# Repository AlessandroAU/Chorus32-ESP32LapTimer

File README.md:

# Changes:

This fork adds an additional PCB option and assosiated software changes to Chorus32, check out the PCB folder [here](pcb/AaronSmith/PCB%20V2) for more hardware details.

# Chorus32-ESP32Laptimer

This is an ESP32 port of the popular Chorus RF laptimer (https://github.com/voroshkov/Chorus-RF-Laptimer). Using an ESP32 provides much more processing power than AVR based Arduino boards and also has built in Wifi and Bluetooth networking simplifying connectivity options.

Compared to the original ChorusRF Lamptimer this ESP32 version only requires one RX module per pilot and a single ESP32 (nodemcu or similar) board. This allows you to connect your Lap timer wirelessly with no extra hardware required. However, due to ADC constraints, we are limited to 6 pilots per device.

Hardware construction is also simplified as both parts are 3.3v logic and there is no need for level shifting or resistors.

[Click HERE for a video showing the full setup process to get Chorus32 running on your ESP32 using Arduino IDE.](https://www.youtube.com/watch?v=ip2HUVk_lMs).

[Click Here for German version Part 1](https://www.youtube.com/watch?v=z8xTfuLECME) [Part 2](https://www.youtube.com/watch?v=7wl0CgA8YnM).

Updates:
-----
*Important Notice for Chorus32 users!!!:*

As of last commit the default pinout has been changed to match that of the PCBs currently being tested.

For anyone that has built a Chorus32 with original schematics do not worry, your unit will continue working with future updates. However you must change `#define BOARD BOARD_DEFAULT` to `#define BOARD BOARD_OLD` in 'HardwareConfig.h' when compiling.

Added OLED and VBAT measurement support
Auto RSSI threshold setup is also not implemented, just set thresholds manually for now.

Added inital webserver configuration portal
https://www.youtube.com/watch?v=BVd2t0yO_5A/0.jpg

Application Support:
-----
Chorus32 communicates using the Chorus RF Laptimer API, which is supported by LiveTime.

LiveTime is an incredibly powerful and feature-rich timing system which runs on Windows. It is, however, quite complex, and likely overkill for most users.

More information can be found here: https://www.livetimescoring.com/

If you are looking for a simpler setup, you can also use the Chorus RF Lap Timer app available for:

Android: https://play.google.com/store/apps/details?id=app.andrey_voroshkov.chorus_laptimer

iOS: https://itunes.apple.com/us/app/chorus-rf-laptimer/id1296647206?mt=8

Serial to UDP bridge.
-----

To use this wirelessly with livetime you must use a third party application to a bridge vitural serial port with the UDP connection to the timer. The native ethernet TCP mode does not work at the moment. You can use this free application https://www.netburner.com/download/virtual-comm-port-driver-windows-xp-10/?fbclid=IwAR2W9V_YzjuP5_u9U-nJx1x38beFWNR0eRI59QOyYO_-NSePmTnW14kk7yA

Configure it like this:

Hardware:
-----
Construction is easy and only requires some basic point to point wiring of each module to the ESP32 board.

See HardwareConfig.h for pin assignments, it is possible to change any pin assignments apart from ADC channels. Note that pin assignments are GPIO hardware pin numbers and not pin numbers specific to the particular ESP32 development board you may be using.

PCB designs are currently being tested

Performance:
-----
The Chorus32 Lap timer was compared to the $600USD ImmersionRC LapRF 8-Way at a local indoor event, arguably the worst conditions due to multipath and reflections. Results are presented below, you can see that the Chorus32 very closely matches the measured lap times of the LapRF.

## Compiling the project using platformio

## Installing
 TODO

## Compiling and uploading

### IDE
TODO

### CLI
To upload the code to your timer just run
```
pio run -e <your board> -t upload
pio run -e <your board> -t uploadfs
```
Insert the board you are using, which is probably `BOARD_DEFAULT`. To list all valid targets just insert some random string as the board (sorry, I have no idea on how to list them properly).

To update using the webpage, run the same commands (and ignore the errors about a failed connection). The path to the file you upload should now be `<project dir>/.pio/build/<BOARD NAME>/firmware.bin`.

## Compiling the Project using the Arduino IDE (the old way):

#### Add esp32 to the Arduino IDE

Navigate to "File -> Preferences" and add "https://dl.espressif.com/dl/package_esp32_index.json" to "Additional Boards Manager URLs". If there is already an entry, just separate them with a ",".

Now navigate to "Tools -> Board -> Boards Manager..." search for "esp32" and click install.

#### Data Upload

To upload the files for the webpage you'll need to download https://github.com/me-no-dev/arduino-esp32fs-plugin/releases/ and extract it in "<Your Arduino install folder>/tools/". So that you end up with a folder called "ESP32FS" which has a folder "tool" inside of it.

#### Libraries

First head to "Sketch -> Include Library -> Manage Libraries" and search for "adafruit ina219" and "ssd1306 esp32" and install them both. Now head to https://github.com/me-no-dev/ESPAsyncWebServer and https://github.com/me-no-dev/AsyncTCP and click on "Clone or download -> Download ZIP". In the Arduino IDE nagivate to "Sketch -> Include Library -> Add .ZIP Library" and add them both.

#### Flashing
Now hit the upload button (with an arrow to the right) to upload the code to the board. After that upload the webpage data by clicking on "Tools -> ESP32 Sketch Data Upload". This should be done on every update!

You can edit file "HardwareConfig.h" to specify your board type and for some advanced configuration.

#### Updating

For updates either follow the normal flashing procedure or use the web UI.
To use the web UI updater open your Arduino IDE and click the verify button (the most left one).
Depending on your operating system there is a folder named "arduino_build_\<some numbers\>" in:
  - Linux: /tmp
  - Windows: %AppData%
  - OSX: No idea, sorry

Inside that folder should be a file called "ESP32LapTimer.ino.bin", which can be uploaded in the web interface.

Library requirements:
-----
Adafruit_INA219 https://github.com/adafruit/Adafruit_INA219

ESP8266 AND ESP32 OLED DRIVER FOR SSD1306 DISPLAY https://github.com/ThingPulse/esp8266-oled-ssd1306

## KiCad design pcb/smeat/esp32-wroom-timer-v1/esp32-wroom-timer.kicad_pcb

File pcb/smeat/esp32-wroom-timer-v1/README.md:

# Features
 - External edge mounted SMA connector for better range
   - Uses the esp32-wroom-32u
   - To connect the antenna, cut open a U.FL adapter cable and solder one end to the SMA connector
 - Integrated buck converter with correct components ;) (those modules from china are all over the place)
    - Max input 28V (26V if using ina219)
 - Footprint for an optional LoRa module
 - Space for 6 RX5808 modules
 - Optional ina219
    - I don't trust them anymore since one failed for me and put the input voltage on the 3.3V rail
    - Limits input voltage to 26V
 - Optional Fan with optional temperature sensor
 - Beeper

# Bugs
 - Wrong SMA footprint (still fits though)
 - Buzzer footprint is a little bit too small for my buzzers
 - A vertically mounted XT60 might be better

# Images

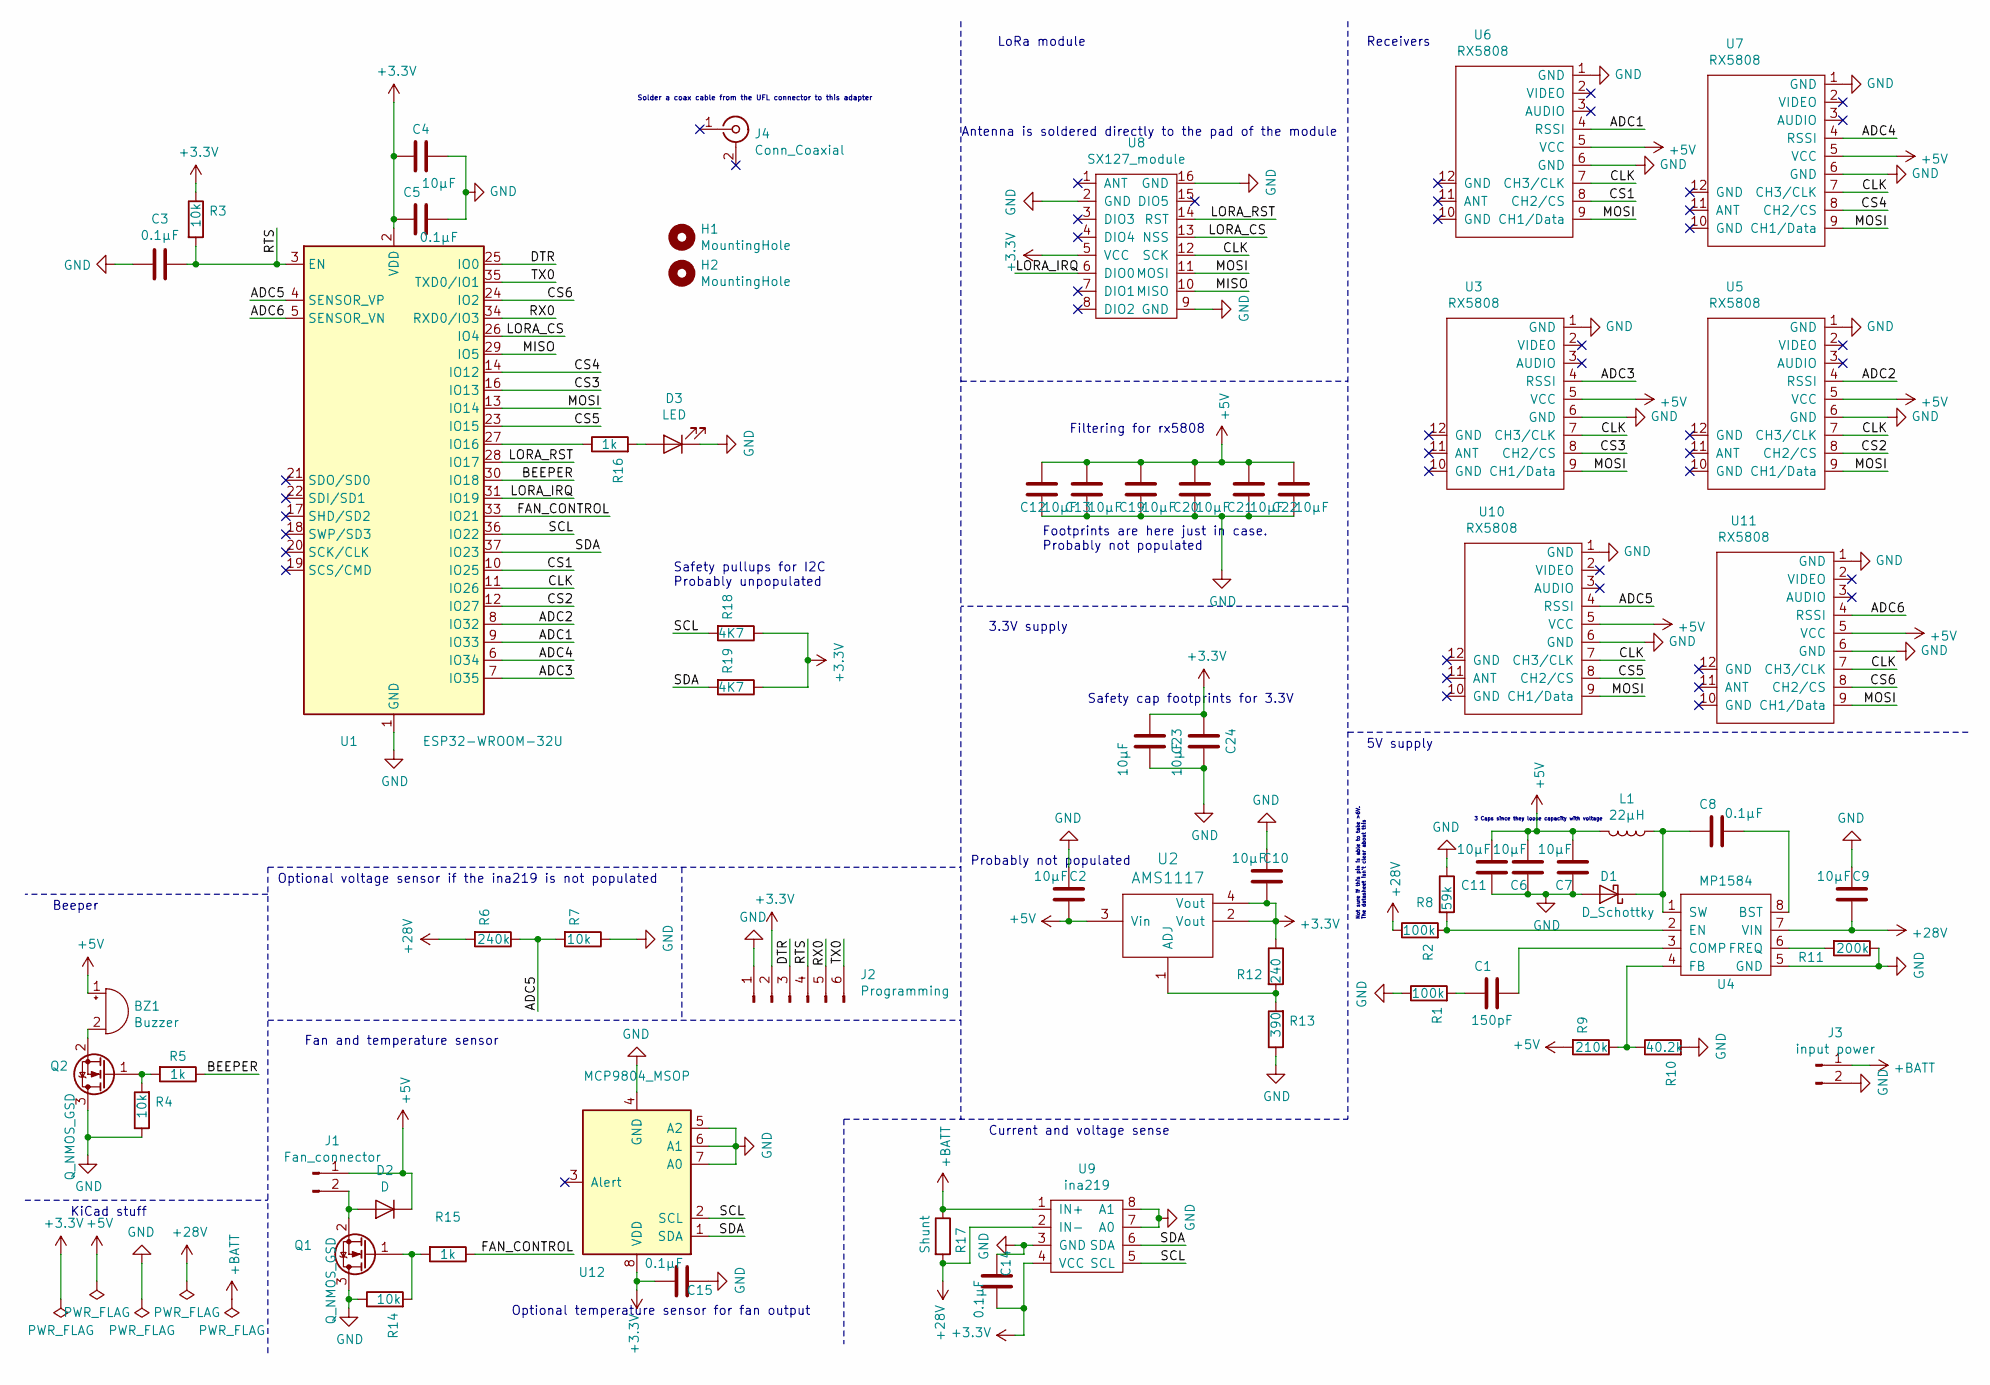
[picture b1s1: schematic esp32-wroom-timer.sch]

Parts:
BZ1: Buzzer; MagneticBuzzer_Kingstate_KCG0601
C1: 150pF; C_0603_1608Metric
C2, C4, C6, C7, C9, C10, C11, C12, C13, C19, C20, C21, C22, C23, C24: 10µF; C_0805_2012Metric
C3, C5, C8, C14, C15: 0.1µF; C_0603_1608Metric
D1: D_Schottky; D_SMA
D2: D; D_SMA
D3: LED; LED_0805_2012Metric
H1, H2: MountingHole; MountingHole_3.2mm_M3
J1: Fan_connector; PinHeader_2x01_P2.00mm_Vertical_SMD
J2: Programming; PinHeader_1x06_P2.00mm_Vertical
J3: input power; SolderWirePad_1x02_P7.62mm_Drill2.5mm
J4: Conn_Coaxial; SMA_Amphenol_132289_EdgeMount
L1: 22µH; L_12x12mm_H6mm
Q1, Q2: Q_NMOS_GSD; SOT-23
R1, R2: 100k; R_0805_2012Metric
R3, R4, R7, R14: 10k; R_0805_2012Metric
R5, R15, R16: 1k; R_0805_2012Metric
R6: 240k; R_0805_2012Metric
R8: 59k; R_0805_2012Metric
R9: 210k; R_0805_2012Metric
R10: 40.2k; R_0805_2012Metric
R11: 200k; R_0805_2012Metric
R12: 240; R_0805_2012Metric
R13: 390; R_0805_2012Metric
R17: Shunt; R_2512_6332Metric
R18, R19: 4K7; R_0805_2012Metric
U1: ESP32-WROOM-32U
U2: AMS1117; SOT-223
U3, U5, U6, U7, U10, U11: RX5808; rx5808
U4: MP1584; SOIC-8_3.9x4.9mm_P1.27mm
U8: SX127_module; sx1276_module
U9: ina219; SOT-23-8
U12: MCP9804_MSOP; MSOP-8_3x3mm_P0.65mm

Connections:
+3V3: C4.2, C5.2, C10.1, C14.1, C15.1, C23.2, C24.2, J2.2, R3.1, R12.1, R18.1, R19.1, U1.2 (VDD), U2.2 (Vout), U2.4 (Vout), U8.5 (VCC), U9.4 (VCC), U12.8 (VDD)
+5V: BZ1.1 (-), C2.1, C6.2, C7.2, C11.2, C12.1, C13.1, C19.1, C20.1, C21.1, C22.1, D2.1 (K), J1.1, L1.2, R9.2, U2.3 (Vin), U3.5 (VCC), U5.5 (VCC), U6.5 (VCC), U7.5 (VCC), U10.5 (VCC), U11.5 (VCC)
+28V: C9.1, R2.1, R6.2, R17.2, U4.7 (VIN), U9.2 (IN-)
+BATT: J3.1, R17.1, U9.1 (IN+)
/ADC1: U1.9 (IO33), U6.4 (RSSI)
/ADC2: U1.8 (IO32), U5.4 (RSSI)
/ADC3: U1.7 (IO35), U3.4 (RSSI)
/ADC4: U1.6 (IO34), U7.4 (RSSI)
/ADC5: R6.1, R7.2, U1.4 (SENSOR_VP), U10.4 (RSSI)
/ADC6: U1.5 (SENSOR_VN), U11.4 (RSSI)
/BEEPER: R5.1, U1.30 (IO18)
/CLK: U1.11 (IO26), U3.7 (CH3/CLK), U5.7 (CH3/CLK), U6.7 (CH3/CLK), U7.7 (CH3/CLK), U8.12 (SCK), U10.7 (CH3/CLK), U11.7 (CH3/CLK)
/CS1: U1.10 (IO25), U6.8 (CH2/CS)
/CS2: U1.12 (IO27), U5.8 (CH2/CS)
/CS3: U1.16 (IO13), U3.8 (CH2/CS)
/CS4: U1.14 (IO12), U7.8 (CH2/CS)
/CS5: U1.23 (IO15), U10.8 (CH2/CS)
/CS6: U1.24 (IO2), U11.8 (CH2/CS)
/DTR: J2.3, U1.25 (IO0)
/FAN_CONTROL: R15.1, U1.33 (IO21)
/LORA_CS: U1.26 (IO4), U8.13 (NSS)
/LORA_IRQ: U1.31 (IO19), U8.6 (DIO0)
/LORA_RST: U1.28 (IO17), U8.14 (RST)
/MISO: U1.29 (IO5), U8.10 (MISO)
/MOSI: U1.13 (IO14), U3.9 (CH1/Data), U5.9 (CH1/Data), U6.9 (CH1/Data), U7.9 (CH1/Data), U8.11 (MOSI), U10.9 (CH1/Data), U11.9 (CH1/Data)
/RTS: C3.1, J2.4, R3.2, U1.3 (EN)
/RX0: J2.5, U1.34 (RXD0/IO3)
/SCL: R18.2, U1.36 (IO22), U9.5 (SCL), U12.2 (SCL)
/SDA: R19.2, U1.37 (IO23), U9.6 (SDA), U12.1 (SDA)
/TX0: J2.6, U1.35 (TXD0/IO1)
GND: C2.2, C3.2, C4.1, C5.1, C6.1, C7.1, C9.2, C10.2, C11.1, C12.2, C13.2, C14.2, C15.2, C19.2, C20.2, C21.2, C22.2, C23.1, C24.1, D1.2 (A), D3.1 (K), J2.1, J3.2, Q1.3 (D), Q2.3 (D), R1.1, R4.1, R7.1, R8.1, R10.2, R11.1, R13.1, R14.1, U1.1 (GND), U1.15 (GND), U1.38 (GND), U3.1 (GND), U3.6 (GND), U4.5 (GND), U5.1 (GND), U5.6 (GND), U6.1 (GND), U6.6 (GND), U7.1 (GND), U7.6 (GND), U8.2 (GND), U8.9 (GND), U8.16 (GND), U9.3 (GND), U9.7 (A0), U9.8 (A1), U10.1 (GND), U10.6 (GND), U11.1 (GND), U11.6 (GND), U12.4 (GND), U12.5 (A2), U12.6 (A1), U12.7 (A0)
unnamed: BZ1.2 (+), Q2.2 (S)
unnamed: C1.1, U4.3 (COMP)
unnamed: C1.2, R1.2
unnamed: C8.1, U4.8 (BST)
unnamed: C8.2, D1.1 (K), L1.1, U4.1 (SW)
unnamed: D2.2 (A), J1.2, Q1.2 (S)
unnamed: D3.2 (A), R16.2
unnamed: Q1.1 (G), R14.2, R15.2
unnamed: Q2.1 (G), R4.2, R5.2
unnamed: R2.2, R8.2, U4.2 (EN)
unnamed: R9.1, R10.1, U4.4 (FB)
unnamed: R11.2, U4.6 (FREQ)
unnamed: R12.2, R13.2, U2.1 (ADJ)
unnamed: R16.1, U1.27 (IO16)

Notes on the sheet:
Antenna is soldered directly to the pad of the module
Filtering for rx5808
Not sure if this pin is able to take >6V. The datasheet isn't clear about this
3 Caps since they loose capacity with voltage
Probably not populated
Footprints are here just in case. Probably not populated
Optional temperature sensor for fan output
KiCad stuff
5V supply
Receivers
Safety cap footprints for 3.3V
3.3V supply
Current and voltage sense
Fan and temperature sensor
Beeper
LoRa module
Optional voltage sensor if the ina219 is not populated
Solder a coax cable from the UFL connector to this adapter
Safety pullups for I2C Probably unpopulated

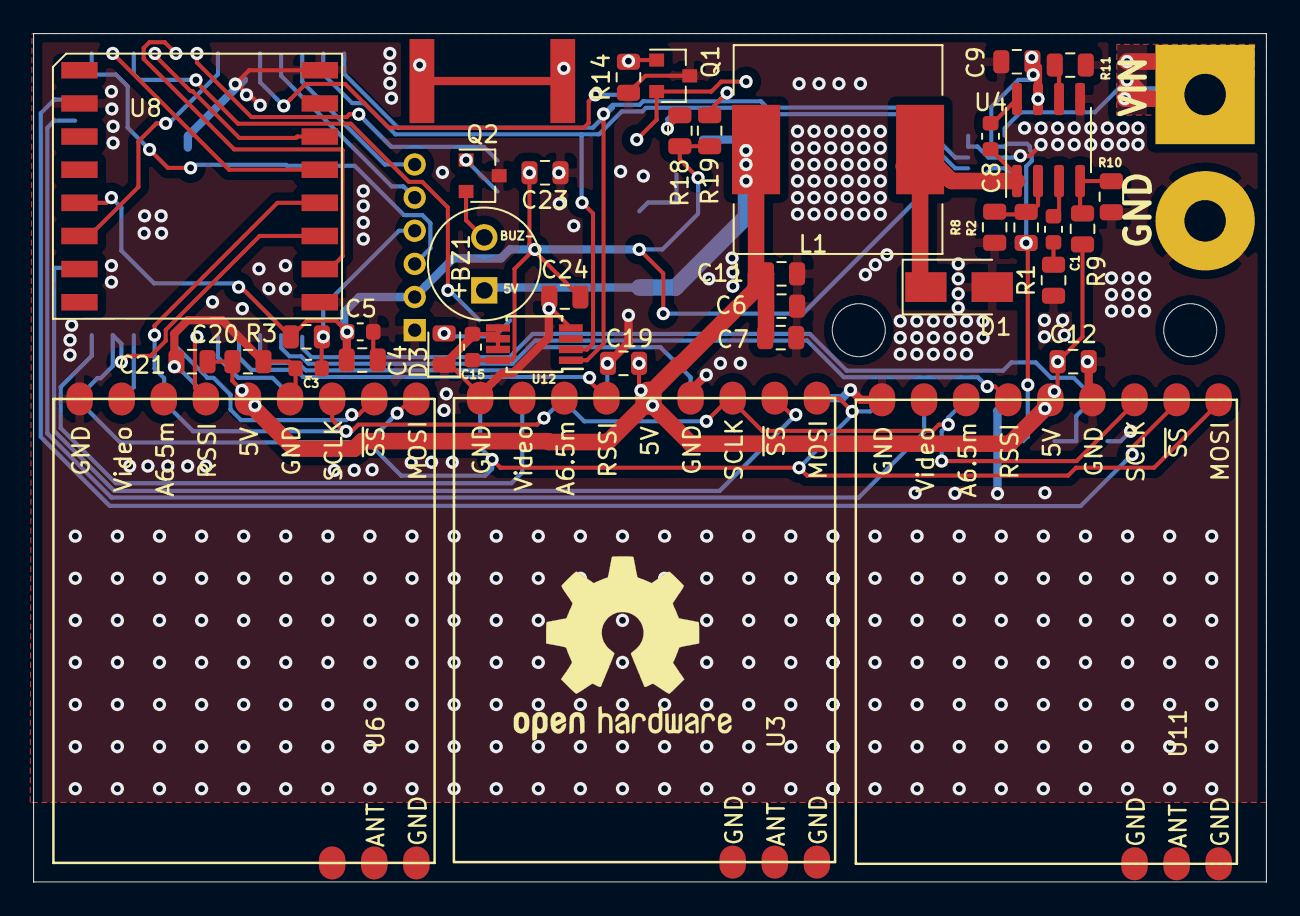
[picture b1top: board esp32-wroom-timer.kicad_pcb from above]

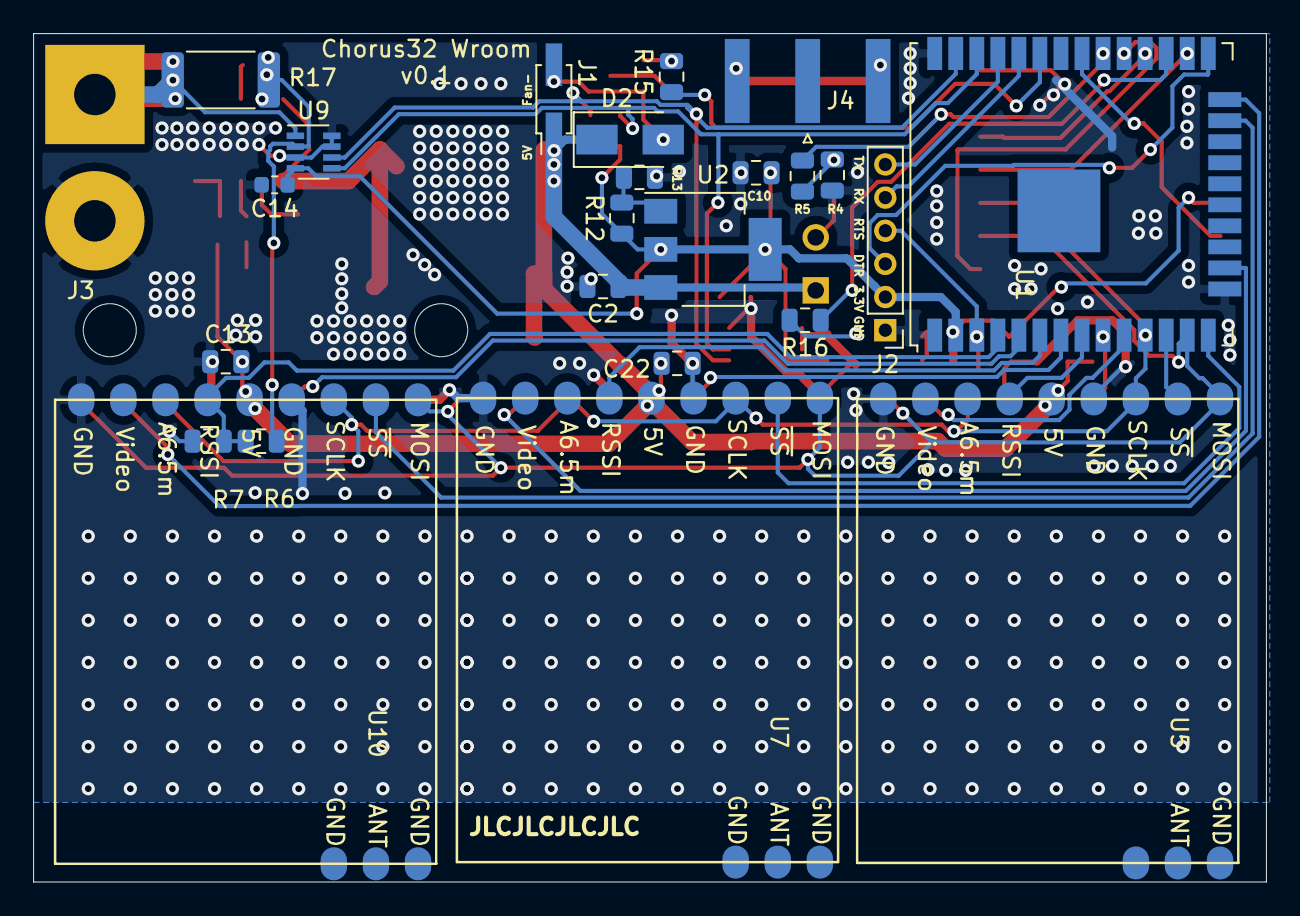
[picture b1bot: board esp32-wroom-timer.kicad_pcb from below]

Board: 2 copper layers, 74.4 x 51.2 mm, 65 parts (25 on the bottom side), 45 nets.

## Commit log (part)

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2018-11-23 Update README.md
    Initial Readme
2018-11-23 Update ESP32LapTimer.ino.esp32.bin
    Updated Precompiled Binary
2019-02-08 Add diagram
    added wiring diagram and code template for eventual eeprom settings storage
2019-02-08 Set theme jekyll-theme-slate
2019-02-12 Fixing Racegod compatibility
2019-02-23 adds oled
    Initial oled implementation.
    TODO - remove oledUpdate() from main loop and add to a timer for updating once a second.
2019-02-24 a little organisation
2019-02-24 fixes oled with another #ifdef AlessandroDevBoard
2019-02-24 initial commit, not working
2019-02-24 Add VBAT reading to comms.ino
2019-02-25 eeprom ready for testing
2019-02-28 Added Webserver
2019-03-02 ina219 fixes
2019-03-02 adds option to use vspi or hspi
2019-03-02 fix spi defines
2019-03-02 6 Ch support
    6 channel RX support
2019-03-02 adds timer
2019-03-02 decrease oled vbat decimals
2019-03-03 adds 6 rx to oled
2019-03-03 Revert "adds 6 rx to oled"
    This reverts commit d66650e8dc6503e8669c6771d1577609d937a84e.
2019-03-03 adds screensaver
2019-03-03 Bug Fix
2019-03-03 Update HardwareConfig.h
    Fixed default #define
2019-03-05 Fixed bug causing crash during race
2019-03-07 increment eeprom
2019-03-07 buttons
    ...because why not?
2019-03-07 Fixed critical bug with timer cal for >4 pilots
2019-03-08 adds beeper
2019-03-08 remove serial print noise
2019-03-10 Fixed multiple readout bug
2019-03-11 Modified sendStatiVars to send rxband and rxchannel
2019-03-11 Added read of RXBand and RXChannel
2019-03-12 fixed some errors, not working yet
2019-03-12 Added library dependencies
2019-03-13 Added threshold line
2019-03-13 Fixed showing incorrect band and channel data on website
2019-03-13 Removed Vbat meassurement if ADCVBATmode == 0
2019-03-14 Changed limits of RSSIThreshold html input
2019-03-19 Improved LiveTime compatiblity and eeprom sanity checking
2019-03-19 first
2019-03-20 Fixed absolute timing for LiveTime
    LiveTime is looking for time since race start, previous code was giving time since Chorus booted up.
2019-03-22 PCB V2 open for comments
2019-03-23 remove AlessandroDevBoard
    Yay its dead!
2019-03-23 clenaup
2019-03-23 adds multiple oled displays for stats, debug info
    Pressing button 1 cycles through the displays.
2019-03-23 fixed default setting
2019-03-23 don't need to set MISO
2019-03-27 General cleanup & more Application Support info
2019-03-28 adds library links
2019-04-01 Revert "Added video walkthrough for Chorus32 Installation via Arduino IDE"
2019-04-01 Revert "Revert "Added video walkthrough for Chorus32 Installation via Arduino IDE""
2019-04-04 Added gerbers & schematic for PCB
2019-04-04 Resolved RSSI<50 artifact
    Added logic to display an RSSI bar for 50 whenever the RSSI drops below 50, resolving the graphic artifact on the OLED display.
2019-04-07 adds rx module calibration
2019-04-07 PCB-V2.1
    https://easyeda.com/jyesmith/alessandroau-chorus32-esp32laptimer_v2-1
2019-04-10 Added CalibrateRSSI and eeprom settings to web interface
2019-04-10 Added Airplane Mode Settings screen
    Added a 4th screen which contains airplane mode settings. Press button 1 until you arrive at screen 4, then press button 2 to toggle Airplane mode on/off. This results in a roughly 10% power savings 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
2019-04-11 Added RX Settings screens
    Added screens dynamically based on the number of RX to be able to view and eventually change RX settings using the buttons.
2019-04-11 Working frequency changes from OLED
    Fixed the issues with changing frequencies from the OLED.
2019-04-13 Buttons.ino refactor
    Cleaned up old code and added additional comments for clarity.
2019-04-15 Button refactor and OLED screen navigation (#60)
    * Buttons and beeps
    New button presses, new screen navigation, new beep types. Need to clean up old button stuff.
    * Buttons.ino refactor
    Cleaned up old code and added additional comments for clarity.
    * Fixed typo
2019-05-16 Removed ifdef to merge master back into this fork
2019-05-16 Buttons pin definitions added
    Needed to enable compliation
2019-05-19 Fix compilation on case sensitive systems. (#62)
2019-06-08 Allow the use of normal input buttons.
2019-06-08 Characterize adc to fight the non-linearity
2019-06-13 Initilise mirco32 pins to default states
2019-06-19 Allow the use of normal input buttons. (#64)
    Thanks :)
2019-06-19 Skip ADC calibration for voltage monitor pin. (#63)
2019-06-25 Characterize adc to fight the non-linearity (#65)
2019-07-04 Added documentation & images
    PCB BOM, readme, assembly and programming data added. Some images of an assembled module also added
2019-07-04 Added fork description to main readme
2019-07-06 Add very simple target management
2019-07-07 Some cleanup in ADC. (#67)
    Mainly removing unused variables and moving some from the header to the source file.
2019-07-07 Move WebServer to cpp.
2019-07-07 Move RX5808 and Buttons to cpp.
2019-07-07 Move comms, OLED and Bluetooth to cpp.
2019-07-07 Move Utils to cpp
2019-07-07 Move Utils to cpp (#71)
2019-07-07 PCB-V2.1 (#53)
    https://easyeda.com/jyesmith/alessandroau-chorus32-esp32laptimer_v2-1
2019-07-07 Refactor input and oled.
2019-07-07 Add setting for WiFi channel and protocol.
2019-07-07 Refactor input and oled. (#74)
2019-07-08 Add support for bluetooth.
2019-07-08 Add support for bluetooth. (#76)
2019-07-08 Some cleanup. (#78)
    Mostly declaring variables as static
2019-07-08 Fix all compiler warnings.
2019-07-08 Fix all compiler warnings. (#79)
2019-07-14 adds patch wire image for pcb v2.1
2019-07-15 Add input for rssi calibration
2019-07-15 Allow compilation without button definition
2019-07-15 Move lap logic to Laptime Fix undefined behavior when requesting lap 0
2019-07-19 Fix compilation with serial output enabled.
2019-07-19 Allow compilation without button definition (#83)
2019-07-19 Set the time adjustment to calibrated. (#84)
    Calibration is not needed since we only have one microcontroller.
2019-07-19 Fix compilation with serial output enabled. (#86)
2019-07-20 Enable serial output by default
2019-07-20 Add LIKELY and UNLIKELY macros. (#87)
    We are obviously way smarter than the compiler ;)
2019-07-20 Enable serial output by default (#89)
2019-07-21 Remove old extern variables.
2019-07-21 Redirect to main page on eeprom reset Also prevents the client from sending multiple reset requests.
2019-07-22 Remove duplicate code in RX5808
2019-07-23 Make max number of laps configurable
2019-07-23 Multisample rssi if not in race mode This reduces noise and is useful for threshold calibration
2019-07-23 Use a function to retrieve number of receivers instead of extern variable Fix typo
2019-07-23 Send all laps when requesting all settings
2019-07-25 Redirect to main page on rssi calibration Prevents the client from sending multiple requests.
2019-07-26 Prevent illegal input for map when drawing the threshold bar Fixes the threshold bar escaping the progress bar
2019-07-26 Name more OLED RSSI values
2019-07-27 Flush outputs when sending all laps and settings
2019-07-27 Replace semaphore with notify to block the ADC task Uses less RAM and is 45% faster
2019-07-27 Fix race condition in output. Handle the sending of laps on a different core to prevent lockups.
2019-07-28 Fix udp socket, when a client disconnects This also directly uses the socket to reduce the dynamic memory allocation
2019-07-28 Fix race condition in output. (#94)
    Handle the sending of laps on a different core to prevent lockups.
2019-07-29 Use crc to validate the EEPROM This improves the ability to detect EEPROM coruption (even if we have no manual check) and forces a reset if the struct gets changed, but the version number is unchange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
2019-07-29 Add support for display timeout (#97)
2019-08-10 Add comment on when to use BOARD_OLD.
2019-08-13 Prevent illegal calibration If, for whatever reason, a modules wouldn't send a value the calibration would end up with max = min = 0, which in result will cause a crash in the map function. This ensu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
2019-08-13 Restructure the hardware configuration and add more comments
2019-08-13 Fix various missing includes after removing extra includes in HardwareConfig.h This also includes renaming the VRX SPI pin definitions, so they won't clash with internal Arduino defines.
2019-08-16 Set the default calibration to the configured max and minimum ADC values.
2019-08-22 Add support for TCP connections. First tests suggested this is far superior to using UDP, but further testing is required. Currently disabled by default.
2019-10-19 Add documentation for compiling and flashing
2019-12-16 platformio env builds
2019-12-16 remove defines that are now contained in .ini
2019-12-24 Move to platformio Full credits to @JyeSmith
2020-03-10 Add travis configuration Builds and uploads releases.
2020-03-14 Fix messed up cherry-pick
2020-03-15 Adding some helper macros for array allocation
2020-03-15 Typo fix
2020-03-15 Increasing maximum number of receivers
    This increases the maximum number receivers to 8 for potential usage
    with a mux chip.
2020-03-15 Renaming MaxNumReceivers
2020-03-15 Added error checking for pin numbers
    Not sure if this is the right file but leaving it here for now.
2020-03-15 Fixes overflow in constant
2020-03-15 Adding new files for wireless config
2020-03-16 Add travis configuration (#103)
    Builds and uploads releases.
2020-03-18 Adding code for running as a WiFi client
2020-03-18 Updating file to reflect new handling of WiFi and HTTP
2020-03-18 Removing unused code
2020-03-18 Adding new configuration options for WiFi modes
2020-03-18 Fix undefined variables
2020-03-19 Changing from serial prints to esp-idf logging
2020-03-20 Removing mDNS service definition
2020-03-20 Very simple reconnection strategy
    This is the simplest reconnection strategy for the client mode i can come up with.
    If the connection is lost the board will reboot since it’s
    unclear how the various sockets we use will react to that
    event this seems like a safer bet and any solution dealing
    with setting up and tearing down sockets in a good way
    seems like way more work than it’s worth.
2020-03-20 Reconnection strategy take two
    If disconnected just keep trying to reconnect forever.
2020-03-21 Remove delay
2020-03-22 Moving error check to target.h
2020-03-22 More spelling mistake fixes
2020-03-22 Setting the system hostname
2020-03-23 Excplicity setting the wifi mode for the client code
2020-03-23 Fixed missing space
2020-03-23 Changed function to static
2020-03-23 Adding support for wifi client mode (#106)
    * Adding new files for wireless config
    * Removing code that's now in Wireless.cpp
    * Removing unused code
    * Renamed function to better reflect purpose
    * Updating file to reflect new handling of WiFi and HTTP
    * Adding new Wireless header
2020-03-23 Simplifying CS pins logic
2020-03-23 Added checking for potential overflow
2020-03-23 Adding basic sanity check to write
2020-03-26 Use an async webserver
2020-03-27 Add support for emergency OTA mode
2020-03-28 Add support for uploading SPIFFS from the recovery page
2020-03-29 Add protection for manual reboot loop
2020-03-29 Add support for (emergency) OTA mode (#109)
    * Add support for emergency OTA mode
    * Add protection for manual reboot loop
2020-03-29 Add support for websocket output
2020-04-03 Add extended commands
2020-04-14 Set the license to GPLv3
2020-05-23 Add pcb based on the esp32-wroom-32u
2020-05-23 Fix crash mode detection
2020-05-24 Fixes CS pins being in the wrong initial state
2020-05-24 Spi fixup (#121)
    * Fixes CS pins being in the wrong initial state
    * Removes unnecessary rx setup
    * Fixes web interface bug
    This fixes the band/channel on the first rx being reset every time it was updated
2020-05-24 Moves the tune time to after the spi transaction is complete
    The system should probably signal that it's done before waiting for the module to complete the switch
2020-06-18 Implement multiplexing
2020-06-18 Disable multiplexing by default
2022-05-29 fix incorrect variable order
2022-07-13 updated Aaron's PCB to latest master
    original https://github.com/AlessandroAU/Chorus32-ESP32LapTimer/pull/72
